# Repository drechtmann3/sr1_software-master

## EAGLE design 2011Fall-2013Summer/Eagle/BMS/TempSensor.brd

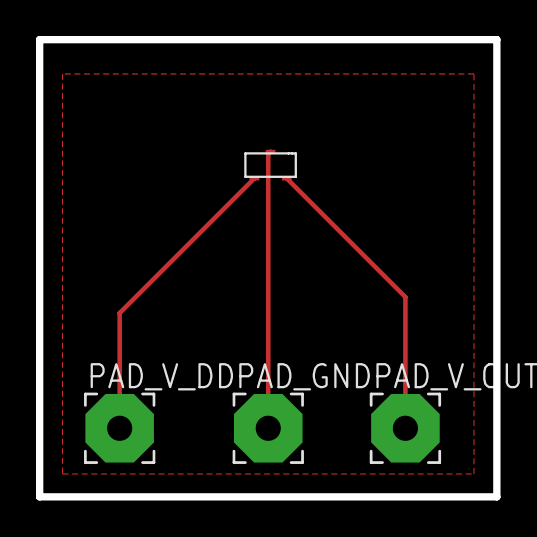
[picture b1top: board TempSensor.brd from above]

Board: 2 copper layers, 25.4 x 25.4 mm, 4 parts (0 on the bottom side), 3 nets.

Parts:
PAD_GND: 3,81/1,4
PAD_V_DD: 3,81/1,4
PAD_V_OUT: 3,81/1,4
U$1: MCP9701-SOT-23

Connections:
unnamed: PAD_V_DD.1, U$1.V_DD
unnamed: PAD_V_OUT.1, U$1.V_OUT
unnamed: PAD_GND.1, U$1.GND

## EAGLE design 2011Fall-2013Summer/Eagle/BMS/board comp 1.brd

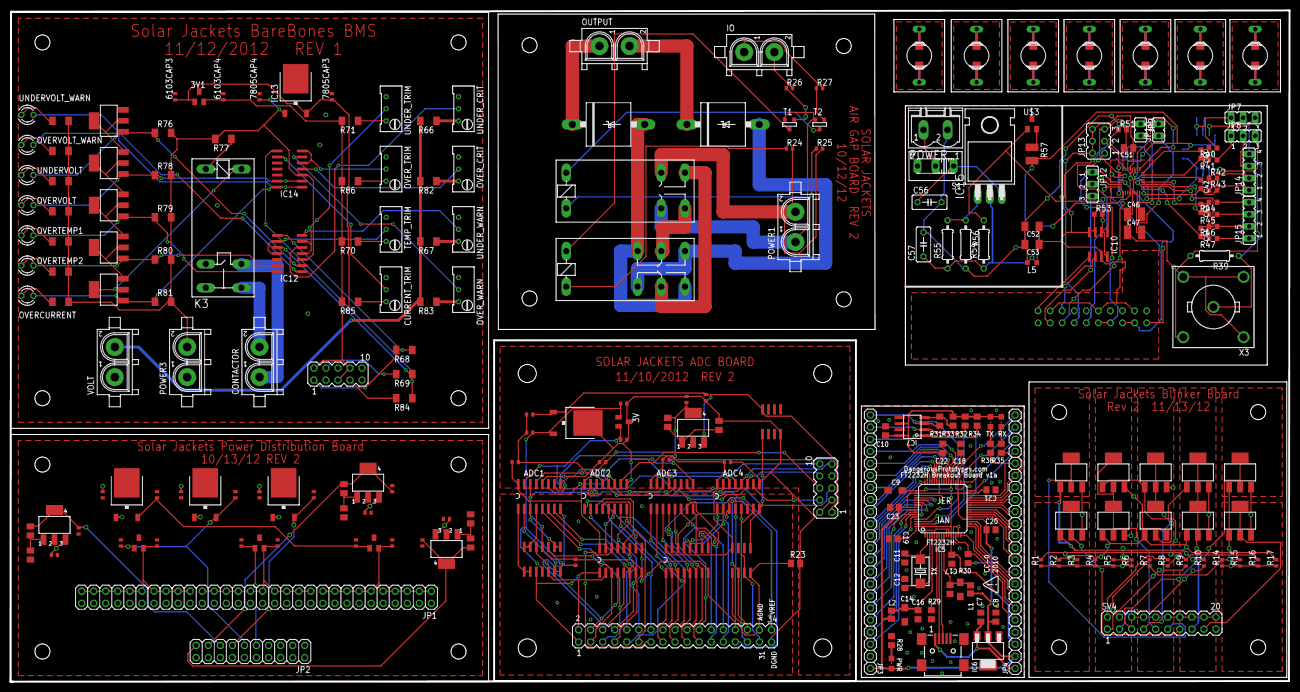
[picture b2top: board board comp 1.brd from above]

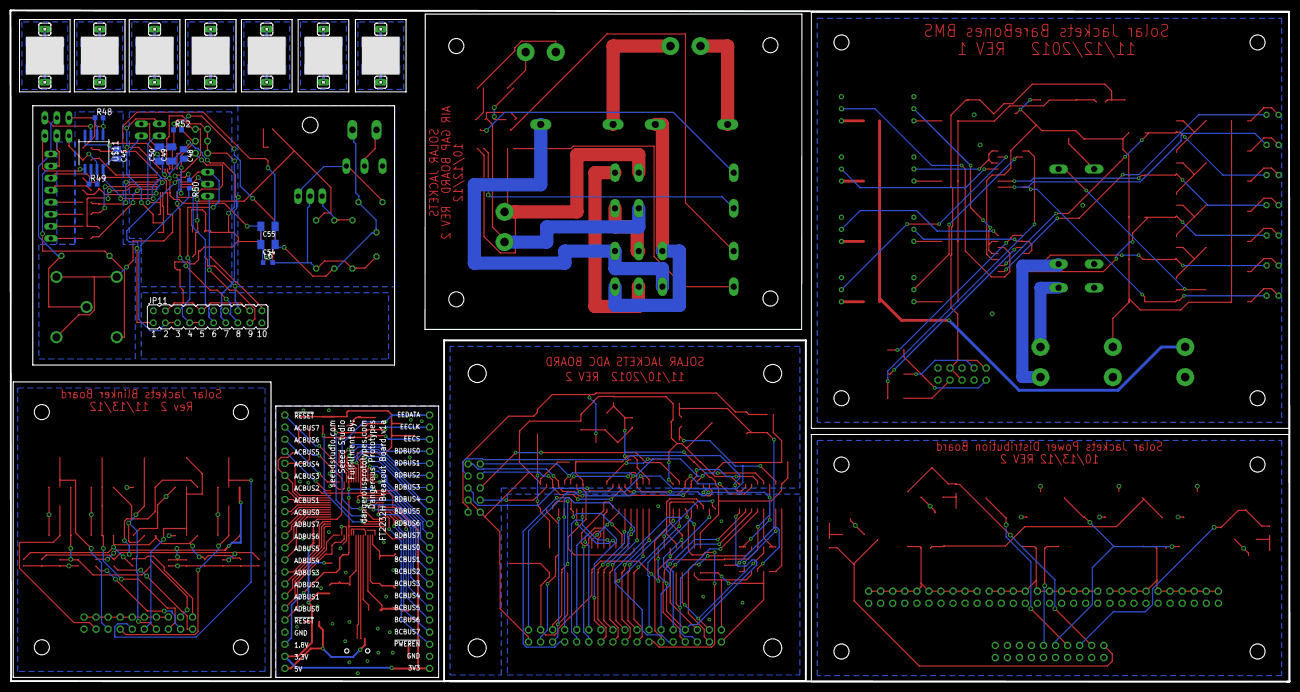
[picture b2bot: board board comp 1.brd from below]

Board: 2 copper layers, 269.4 x 141.4 mm, 280 parts (34 on the bottom side), 264 nets.

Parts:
3V, 3V1, 3V2, 3V3, 3V4: MAX6103; SOT23
5V: LM7805TV; TO252
317CAP1, 317CAP3, 317CAP5, 317CAP7, 7805CAP1: .33uF; C0402
317CAP2, 317CAP4, 317CAP6, 317CAP8, 6103CAP1, 6103CAP2, 6103CAP3, 6103CAP4, 6103CAP5, 6103CAP6, 6103CAP7, 6103CAP8, 6103CAP9, 6103CAP10, 7805CAP2, 7805CAP3, 7805CAP4: 1uF; C0402
6484CAP1: .1uF; C0402
ADC1, ADC2, ADC3, ADC4: MCP-3008; SO16
ADC_CAP1, ADC_CAP2, ADC_CAP3, ADC_CAP4: .1uF; C0402
BLINKER-L1, BLINKER-L2: N-HEXFET-2D_SOT232-; SOT223
BLINKER-R1, BLINKER-R2: N-HEXFET-2D_SOT232-; SOT223
BRAKE-C1, BRAKE-C2: N-HEXFET-2D_SOT232-; SOT223
BRAKE-L1, BRAKE-L2: N-HEXFET-2D_SOT232-; SOT223
BRAKE-R1, BRAKE-R2: N-HEXFET-2D_SOT232-; SOT223
C1, C2, C3, C4, C5, C6: 1uF; C0402
C7, C8, C10, C15, C16, C17, C18, C19, C20, C21, C22, C23: 0.1uF; C805
C9: 3.3uF; SMC_A
C11, C12: 27pF; C805
C13, C14: 4.7uF; SMC_A
C41, C42, C43, C44: 3900pF; C0603K
C45, C48, C51: 1uF; C0805K
C46, C47: 10uF; C1210K
C49, C50, C52, C53, C54, C55: 0.1uF; C1206K
C56, C57: C050-030X075
CONN1: CONN_USB; CONN_USB_MINI-B
CONTACTOR: 350428-1
CURRENT_TRIM: 1k; RTRIM64W
D1, D2: 5KPXX; P6T15
IC1, IC2, IC3, IC4: LM317; SOT223
IC5: FT2232H; LQFP64
IC6: SOT223
IC7: 93C46; SOIC8
IC10: 24LC256T; SO-08
IC12, IC14: LM339D; SO14
IC13: 7805DT; TO252
IC15: 317T; TO220H
IO: 350428-1
JP1: 2X30
JP2: 2X10
JP3, JP4: 1X22
JP7, JP8, JP12: JP2
JP9, JP10: JP1
JP11: JP10Q
JP13: JP3Q
JP14, JP15: JP4
K1: G2R2
K2: G2R2A
K3: G2REA
L1, L2: FB805
L5, L6: L2012C
LMC6484_1: LMC6484; SO14
NEWBATT, NEWBATT1, NEWBATT2, NEWBATT3, NEWBATT4, NEWBATT5, NEWBATT6: LQH55PN220MR0L
OLDBATT, OLDBATT1, OLDBATT2, OLDBATT3, OLDBATT4, OLDBATT5, OLDBATT6: NRS8040T0R9NJGJ
OUTPUT: 350428-1
OVERCURRENT: TLLG4400; LED3MM
OVERCURRENT_FET: N-HEXFET-2D_SOT232-; SOT223
OVERTEMP1, OVERTEMP2: TLLG4400; LED3MM
OVERTEMP1_FET, OVERTEMP2_FET: N-HEXFET-2D_SOT232-; SOT223
OVERVOLT: TLLG4400; LED3MM
OVERVOLT_FET: N-HEXFET-2D_SOT232-; SOT223
OVERVOLT_WARN: TLLG4400; LED3MM
OVER_CRIT: 10k; RTRIM64W
OVER_TRIM: 1k; RTRIM64W
OVER_WARN: 10K; RTRIM64W
POWER: MSTBV2
POWER1, POWER3: 350428-1
PWR: LED-805
PWR_1, PWR_2, PWR_3: 7805DT; TO252
R1, R2, R3, R4, R5, R6, R14, R15, R16, R17, R24, R25, R26, R27: 1k; R0402
R7, R8, R9, R10: 1K; R0402
R11, R13, R19, R21: 220; M0805
R12, R18, R20, R22: 361; M0805
R23: 0; M0805
R28, R35, R36: 470; R805
R29: 12k 1%; R805
R30, R32, R33, R34: 10k; R805
R31: 2.2k; R805
R39: 1M; 0207/10
R40, R41, R42, R43, R44, R45, R46, R47, R48, R49: 49.9; R0603
R50, R53: 33; R0603
R51, R52: 10K; R0603
R54: 150; 0207/10
R55: 240; 0207/10
R56: 725; 0207/10
R57: 0; R3225
R66, R67, R82, R83: 100k; M1406
R68, R69, R70, R71, R77, R85, R86: 100; M1406
R72, R73, R74, R75, R76, R78, R79, R80, R81, R84, R87, R88, R89: 1k; M1406
RX: LED-805
S1: 255SB
SV1: MA17-2
SV2, SV3: MA05-2
SV4: MA10-2
T1, T2: SOT-23
TEMP_TRIM: 1k; RTRIM64W
TX: LED-805
U$1: LM35; SO-08
U$2: ADS8386; ADS8363
U$3: LM4040; SOT23
U$4: DP_LOGO
U$5, U$9, U$10, U$12, U$13, U$14, U$15, U$16, U$17, U$18, U$19, U$20, U$21, U$22: SINGLE_HEADER
U$6, U$7: SP720APP; SO16
U$8: SP721APP; SO-08
U$11: OPA2365; SOP-08
UNDERVOLT: TLLG4400; LED3MM
UNDERVOLT_FET: N-HEXFET-2D_SOT232-; SOT223
UNDERVOLT_WARN: TLLG4400; LED3MM
UNDER_CRIT: 10k; RTRIM64W
UNDER_TRIM: 1k; RTRIM64W
UNDER_WARN: 10K; RTRIM64W
VOLT: 350428-1
X1: 12MHz; 4X6
X3: B35N57

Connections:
1.8V: C9.+, C17.1, C18.1, C19.1, IC5.12, IC5.37, IC5.49, IC5.64, JP4.3
3.3V: 317CAP2.1, ADC1.16, ADC2.16, ADC3.16, ADC4.16, ADC_CAP1.1, ADC_CAP2.1, ADC_CAP3.1, ADC_CAP4.1, IC4.4, R21.1, U$6.16, U$7.16, U$8.8
3.3V1: 317CAP8.1, IC3.4, JP2.19, R19.1
3.3V2: 317CAP4.1, IC2.4, JP2.15, R11.1
3.3V3: C8.1, C10.1, C20.1, C21.1, C22.1, C23.1, IC5.20, IC5.31, IC5.42, IC5.50, IC5.56, IC6.2, IC7.6, IC7.8, JP3.1, JP4.2, L1.2, L2.2, PWR.A, R30.1, R32.2, R33.2, R34.2, RX.A, TX.A
3.3V4: 317CAP6.1, IC1.4, JP2.17, R13.1
3.3V+: IC10.2, IC10.8, R53.2, R54.2, U$3.1
5V: 3V2.1, 6103CAP5.1, C2.1, PWR_1.2
5V1: C6.1, JP2.13, PWR_3.2
5V2: 3V.1, 5V.2, 6103CAP1.1, 6484CAP1.1, 7805CAP2.1, LMC6484_1.4
5V3: 3V1.1, 6103CAP3.1, 7805CAP3.1, IC13.2, SV3.2, SV3.5, SV3.8
5V4: 3V3.1, 6103CAP7.1, JP2.9
5V5: 3V4.1, 6103CAP9.1, C4.1, JP2.11, PWR_2.2
5V6: C7.1, CONN1.VUSB, IC6.3, JP4.1
5V+: C45.2, C48.2, C49.2, C50.2, C54.2, C55.2, L6.1, U$2.P$13_, U$2.P$29_, U$11.8
12V: 5V.1, 317CAP1.1, 7805CAP1.1, IC4.3, SV2.1, U$1.8
12V1: K2.P1, POWER1.2, R24.2, R25.2
12V2: 7805CAP4.1, IC12.3, IC13.1, IC14.3, POWER3.2, R72.2, R73.2, R74.2, R75.2, R76.2, R77.2, R78.2, R79.2, R80.2, R81.2, R87.2, R88.2, R89.2
12V3: SV4.6, SV4.8, SV4.10, SV4.12, SV4.14, SV4.16, SV4.18, SV4.20
12V4: 317CAP3.1, 317CAP5.1, 317CAP7.1, C1.1, C3.1, C5.1, IC1.3, IC2.3, IC3.3, JP2.1, JP2.3, JP2.5, JP2.7, PWR_1.1, PWR_2.1, PWR_3.1
96V: R66.2, R67.2, R82.2, R83.2, VOLT.2
!PWEREN: IC5.60, JP3.3
!RESET: IC5.14, JP4.5, R30.2
!SUSPEND: IC5.36, JP4.22
A1: ADC1.1, LMC6484_1.1, LMC6484_1.2
A2: ADC1.2, LMC6484_1.6, LMC6484_1.7
A3: ADC1.3, LMC6484_1.8, LMC6484_1.9
A4: ADC1.4, LMC6484_1.13, LMC6484_1.14
AC0: IC5.26, JP4.14
AC1: IC5.27, JP4.15
AC2: IC5.28, JP4.16
AC3: IC5.29, JP4.17, R35.1
AC4: IC5.30, JP4.18, R36.1
AC5: IC5.32, JP4.19
AC6: IC5.33, JP4.20
AC7: IC5.34, JP4.21
AD0: IC5.16, JP4.6
AD1: IC5.17, JP4.7
AD2: IC5.18, JP4.8
AD3: IC5.19, JP4.9
AD4: IC5.21, JP4.10
AD5: IC5.22, JP4.11
AD6: IC5.23, JP4.12
AD7: IC5.24, JP4.13
AGND: 6484CAP1.2, ADC1.14, ADC2.14, ADC3.14, ADC4.14, LMC6484_1.11, R23.1, SV1.32, U$6.8, U$7.8, U$8.4
BC0: IC5.48, JP3.11
BC1: IC5.52, JP3.10
BC2: IC5.53, JP3.9
BC3: IC5.54, JP3.8
BC4: IC5.55, JP3.7
BC5: IC5.57, JP3.6
BC6: IC5.58, JP3.5
BC7: IC5.59, JP3.4
BD0: IC5.38, JP3.19
BD1: IC5.39, JP3.18
BD2: IC5.40, JP3.17
BD3: IC5.41, JP3.16
BD4: IC5.43, JP3.15
BD5: IC5.44, JP3.14
BD6: IC5.45, JP3.13
BD7: IC5.46, JP3.12
BLINKER_L: BLINKER-L1.1, BLINKER-L2.1, R5.2, R6.2, R10.2
BLINKER_L_BACK_-: BLINKER-L2.2, BLINKER-L2.4, SV4.13
BLINKER_L_FRONT_-: BLINKER-L1.2, BLINKER-L1.4, SV4.11
BLINKER_R: BLINKER-R1.1, BLINKER-R2.1, R7.1, R14.2, R15.2
BLINKER_R_BACK_-: BLINKER-R2.2, BLINKER-R2.4, SV4.17
BLINKER_R_FRONT_-: BLINKER-R1.2, BLINKER-R1.4, SV4.15
BRAKE: BRAKE-C1.1, BRAKE-L1.1, BRAKE-R1.1, R1.2, R3.2, R9.2, R16.2
BRAKE_C_-: BRAKE-C1.2, BRAKE-C1.4, BRAKE-C2.2, BRAKE-C2.4, SV4.7
BRAKE_L_-: BRAKE-L1.2, BRAKE-L1.4, BRAKE-L2.2, BRAKE-L2.4, SV4.9
BRAKE_REGEN: BRAKE-C2.1, BRAKE-L2.1, BRAKE-R2.1, R2.2, R4.2, R8.1, R17.2
BRAKE_R_-: BRAKE-R1.2, BRAKE-R1.4, BRAKE-R2.2, BRAKE-R2.4, SV4.5
CONTACTOR_IN: CONTACTOR.2, K3.S@
CONTACTOR_OUT: CONTACTOR.1, K3.P@
CURRENT: R84.2, SV3.7
D5V+: C51.2, C52.2, C53.2, L5.2, R51.2, R52.2, U$2.P$27_
DC+: POWER.1, S1.2
DGND0: C51.1, C52.1, C53.1, IC10.1, IC10.3, IC10.4, IC10.7, JP11.4, JP11.10, JP11.18, JP13.2, JP13.4, JP13.6, R53.1, U$2.P$28_
DIR: IO.2, R26.2
DM: CONN1.D-, IC5.7
DP: CONN1.D+, IC5.8
EECLK: IC5.62, IC7.2, JP3.21, R32.1
EECS: IC5.63, IC7.1, JP3.20, R34.1
EEDATA: IC5.61, IC7.3, JP3.22, R31.2
GND: BLINKER-L1.3, BLINKER-L2.3, BLINKER-R1.3, BLINKER-R2.3, BRAKE-C1.3, BRAKE-C2.3, BRAKE-L1.3, BRAKE-L2.3, BRAKE-R1.3, BRAKE-R2.3, R1.1, R2.1, R3.1, R4.1, R5.1, R6.1, R14.1, R15.1, R16.1, R17.1, SV4.19
GND0: C45.1, C46.1, C47.1, C48.1, C49.1, C50.1, C54.1, C55.1, C56.2, C57.2, POWER.2, R56.2, R57.2, U$2.P$11_, U$2.P$12_, U$2.P$30_, U$11.4, X3.3, X3.4, X3.5
GND1: 3V2.3, 3V3.3, 3V4.3, 317CAP3.2, 317CAP4.2, 317CAP5.2, 317CAP6.2, 317CAP7.2, 317CAP8.2, 6103CAP5.2, 6103CAP6.2, 6103CAP7.2, 6103CAP8.2, 6103CAP9.2, 6103CAP10.2, C1.2, C2.2, C3.2, C4.2, C5.2, C6.2, JP1.2, JP1.4, JP1.6, JP1.8, JP1.10, JP1.12, JP1.14, JP1.16, JP1.18, JP1.20, JP1.22, JP1.24, JP1.26, JP1.28, JP1.30, JP1.32, JP1.34, JP1.36, JP1.38, JP1.40, JP1.42, JP1.44, JP1.46, JP1.48, JP1.50, JP1.52, JP1.54, JP1.56, JP1.58, JP1.60, JP2.2, JP2.4, JP2.6, JP2.8, JP2.10, JP2.12, JP2.14, JP2.16, JP2.18, JP2.20, PWR_1.3, PWR_2.3, PWR_3.3, R12.2, R18.2, R20.2
GND4: R57.1, U$3.2
GND5: 3V.3, 5V.3, 317CAP1.2, 317CAP2.2, 6103CAP1.2, 6103CAP2.2, 7805CAP1.2, 7805CAP2.2, ADC1.9, ADC2.9, ADC3.9, ADC4.9, ADC_CAP1.2, ADC_CAP2.2, ADC_CAP3.2, ADC_CAP4.2, R22.2, R23.2, SV1.33, SV2.2, SV2.3, U$1.4
GND6: K2.P2, POWER1.1, T1.2, T2.2
GND7: C7.2, C8.2, C9.-, C10.2, C11.2, C12.2, C13.-, C14.-, C15.2, C16.2, C17.2, C18.2, C19.2, C20.2, C21.2, C22.2, C23.2, CONN1.GND, IC5.1, IC5.5, IC5.10, IC5.11, IC5.13, IC5.15, IC5.25, IC5.35, IC5.47, IC5.51, IC6.1, IC7.5, JP3.2, JP4.4, R28.1, R29.1
GND8: 3V1.3, 6103CAP3.2, 6103CAP4.2, 7805CAP3.2, 7805CAP4.2, CURRENT_TRIM.1, IC12.12, IC13.3, IC14.12, OVER_CRIT.1, OVER_TRIM.1, OVER_WARN.1, POWER3.1, SV3.3, SV3.6, SV3.9, TEMP_TRIM.1, UNDERVOLT_FET.3, UNDER_CRIT.1, UNDER_TRIM.1, UNDER_WARN.1, VOLT.1
IN1: LMC6484_1.3, SV1.1, U$6.1
IN2: LMC6484_1.5, SV1.2, U$6.2
IN3: LMC6484_1.10, SV1.3, U$6.3
IN4: LMC6484_1.12, SV1.4, U$6.4
IN5: ADC1.5, SV1.5, U$6.5
IN6: ADC1.6, SV1.6, U$6.6
IN7: ADC1.7, SV1.7, U$6.7
IN8: ADC1.8, SV1.8, U$6.9
IN9: ADC2.1, SV1.9, U$6.10
IN10: ADC2.2, SV1.10, U$6.11
IN11: ADC2.3, SV1.11, U$6.12
IN12: ADC2.4, SV1.12, U$6.13
IN13: ADC2.5, SV1.13, U$6.14
IN14: ADC2.6, SV1.14, U$6.15
IN15: ADC2.7, SV1.15, U$7.1
IN16: ADC2.8, SV1.16, U$7.2
IN17: ADC3.1, SV1.17, U$7.3
IN18: ADC3.2, SV1.18, U$7.4
IN19: ADC3.3, SV1.19, U$7.5
IN20: ADC3.4, SV1.20, U$7.6
IN21: ADC3.5, SV1.21, U$7.7
IN22: ADC3.6, SV1.22, U$7.9
IN23: ADC3.7, SV1.23, U$7.10
IN24: ADC3.8, SV1.24, U$7.11
IN25: ADC4.1, SV1.25, U$7.12
IN26: ADC4.2, SV1.26, U$7.13
IN27: ADC4.3, SV1.27, U$7.14
IN28: ADC4.4, SV1.28, U$7.15
IN29: ADC4.5, SV1.29, U$8.1
IN30: ADC4.6, SV1.30, U$8.2
IN31: ADC4.7, SV1.31, U$8.3
IN32: ADC4.8, U$1.1, U$8.5
MOTOR+: D2.C, OUTPUT.2
MOTOR+_PRE: D2.A, K1.O2, K1.S1
MOTOR-: D1.C, OUTPUT.1
MOTOR-_PRE: D1.A, K1.O1, K1.S2
unnamed: R8.2, SV4.2
unnamed: R7.2, SV4.4
unnamed: R9.1, SV4.1
unnamed: R10.1, SV4.3
unnamed: IC2.1, R11.2, R12.1
unnamed: IC1.1, R13.2, R18.1
unnamed: IC3.1, R19.2, R20.1
unnamed: IC4.1, R21.2, R22.1
unnamed: K1.P2, K2.S1
unnamed: K1.P1, K2.S2
unnamed: K1.1, R24.1
unnamed: K2.1, R25.1
unnamed: K1.2, T1.1
unnamed: K2.2, T2.1
unnamed: R27.1, T2.3
unnamed: R26.1, T1.3
unnamed: IC5.6, R29.2
unnamed: C11.1, IC5.2, X1.1
unnamed: C12.1, IC5.3, X1.2
unnamed: PWR.C, R28.2
unnamed: R35.2, RX.C
unnamed: R36.2, TX.C
unnamed: C41.1, R40.2, U$2.P$1_
unnamed: C41.2, R41.2, U$2.P$2_
unnamed: C42.1, R42.2, U$2.P$3_
unnamed: C42.2, R43.2, U$2.P$4_
unnamed: C43.1, R44.2, U$2.P$5_
unnamed: C43.2, R45.2, U$2.P$6_
unnamed: C44.1, R46.2, U$2.P$7_
unnamed: C44.2, R47.2, U$2.P$8_
unnamed: JP7.1, R40.1, R48.2, U$11.1
unnamed: R48.1, U$11.2
unnamed: JP7.3, U$11.3
unnamed: JP8.1, R41.1, R49.2, U$11.7
unnamed: R49.1, U$11.6
unnamed: JP8.3, U$11.5
unnamed: JP14.2, R42.1
unnamed: JP14.1, R43.1
unnamed: JP15.4, R44.1
unnamed: JP15.3, R45.1
unnamed: JP15.2, R46.1
unnamed: JP15.1, R47.1
unnamed: C46.2, JP9.2, U$2.P$9_
unnamed: JP9.1, U$2.P$32_
unnamed: IC7.4, R31.1, R33.1
unnamed: JP10.2, U$2.P$31_
unnamed: C47.2, JP10.1, U$2.P$10_
unnamed: C14.+, C16.1, IC5.4, L2.1
unnamed: C13.+, C15.1, IC5.9, L1.1
unnamed: JP11.1, U$2.P$21_
unnamed: R50.1, U$2.P$22_
unnamed: JP11.3, JP11.5, R50.2
unnamed: JP11.7, JP11.9, JP12.1, U$2.P$20_
unnamed: JP11.11, U$2.P$18_
unnamed: JP11.13, U$2.P$25_
unnamed: JP11.15, U$2.P$23_
unnamed: JP12.2, U$2.P$19_
unnamed: JP11.17, JP12.3
unnamed: JP13.1, U$2.P$16_
unnamed: JP13.3, R51.1, U$2.P$17_
unnamed: JP13.5, R52.1, U$2.P$24_
unnamed: IC10.5, JP11.20
unnamed: IC10.6, JP11.16
unnamed: C57.1, IC15.2, L5.1, L6.2, R54.1, R55.1
unnamed: IC15.1, R55.2, R56.1
unnamed: C56.1, IC15.3, S1.1
unnamed: NEWBATT.P$2, OLDBATT.P$2, U$5.P$1
unnamed: NEWBATT.P$1, OLDBATT.P$1, U$9.P$1
unnamed: NEWBATT1.P$2, OLDBATT1.P$2, U$10.P$1
unnamed: NEWBATT1.P$1, OLDBATT1.P$1, U$12.P$1
unnamed: NEWBATT2.P$2, OLDBATT2.P$2, U$13.P$1
unnamed: NEWBATT2.P$1, OLDBATT2.P$1, U$14.P$1
unnamed: NEWBATT3.P$2, OLDBATT3.P$2, U$15.P$1
unnamed: NEWBATT3.P$1, OLDBATT3.P$1, U$16.P$1
unnamed: NEWBATT4.P$2, OLDBATT4.P$2, U$17.P$1
unnamed: NEWBATT4.P$1, OLDBATT4.P$1, U$18.P$1
unnamed: NEWBATT5.P$2, OLDBATT5.P$2, U$19.P$1
unnamed: NEWBATT5.P$1, OLDBATT5.P$1, U$20.P$1
unnamed: NEWBATT6.P$2, OLDBATT6.P$2, U$21.P$1
unnamed: NEWBATT6.P$1, OLDBATT6.P$1, U$22.P$1
unnamed: IC12.7, UNDER_WARN.2
unnamed: IC12.5, UNDER_CRIT.2
unnamed: IC12.9, IC12.11, TEMP_TRIM.2
unnamed: R66.1, UNDER_CRIT.3
unnamed: R67.1, UNDER_WARN.3
unnamed: IC12.4, IC12.6, UNDER_TRIM.2
unnamed: R71.1, UNDER_TRIM.3
unnamed: R70.1, TEMP_TRIM.3
unnamed: R72.1, UNDERVOLT.A
unnamed: R73.1, UNDERVOLT_WARN.A
unnamed: OVERTEMP1.A, R74.1
unnamed: OVERTEMP2.A, R75.1
unnamed: K3.1, R77.1
unnamed: CURRENT_TRIM.2, IC14.9
unnamed: OVER_WARN.3, R83.1
unnamed: IC14.5, IC14.7, OVER_TRIM.2
unnamed: OVER_TRIM.3, R86.1
unnamed: CURRENT_TRIM.3, R85.1
unnamed: OVERVOLT.A, R87.1
unnamed: OVERVOLT_WARN.A, R88.1
unnamed: OVERCURRENT.A, R89.1
unnamed: K3.2, OVERCURRENT_FET.2, OVERCURRENT_FET.4
unnamed: OVERCURRENT_FET.3, OVERTEMP2_FET.2, OVERTEMP2_FET.4
unnamed: OVERTEMP1_FET.2, OVERTEMP1_FET.4, OVERTEMP2_FET.3
unnamed: OVERTEMP1_FET.3, OVERVOLT_FET.2, OVERVOLT_FET.4
unnamed: OVERVOLT_FET.3, UNDERVOLT_FET.2, UNDERVOLT_FET.4
unnamed: IC14.6, OVER_WARN.2
unnamed: IC14.4, OVER_CRIT.2
unnamed: OVER_CRIT.3, R82.1
unnamed: IC14.8, R84.1
unnamed: IC12.8, R68.1
unnamed: IC12.10, R69.1
ON: IO.1, R27.2
OVERCURRENT_CRITICAL: IC14.14, OVERCURRENT.K, OVERCURRENT_FET.1, R81.1
OVERTEMP_CRITICAL1: IC12.14, OVERTEMP1.K, OVERTEMP1_FET.1, R79.1
OVERTEMP_CRITICAL2: IC12.13, OVERTEMP2.K, OVERTEMP2_FET.1, R80.1
OVERVOLT_CRITICAL: IC14.2, OVERVOLT.K, OVERVOLT_FET.1, R78.1
OVERVOLT_WARNING1: IC14.1, OVERVOLT_WARN.K
SIGNALGND: JP8.2, JP14.3, R39.2, X3.2
SIGNALV+: JP7.2, JP14.4, R39.1, X3.1
SPI_CLK: ADC1.13, ADC2.13, ADC3.13, ADC4.13, SV2.10
SPI_CS1: ADC1.10, SV2.7
SPI_CS2: ADC2.10, SV2.6
SPI_CS3: ADC3.10, SV2.5
SPI_CS4: ADC4.10, SV2.4
SPI_DIN: ADC1.11, ADC2.11, ADC3.11, ADC4.11, SV2.8
SPI_DOUT: ADC1.12, ADC2.12, ADC3.12, ADC4.12, SV2.9
TEMP1: R68.2, SV3.1
TEMP2: R69.2, SV3.4
UNDERVOLT_CRITICAL: IC12.2, R76.1, UNDERVOLT.K, UNDERVOLT_FET.1
UNDERVOLT_WARNING: IC12.1, UNDERVOLT_WARN.K
VREF: 3V.2, 6103CAP2.1, ADC1.15, ADC2.15, ADC3.15, ADC4.15, SV1.34
VREF1: 3V1.2, 6103CAP4.1, R70.2, R71.2, R85.2, R86.2
VREF2: 3V2.2, 6103CAP6.1, JP1.1, JP1.3, JP1.5, JP1.7, JP1.9, JP1.11, JP1.13, JP1.15, JP1.17, JP1.19
VREF3: 3V3.2, 6103CAP8.1, JP1.21, JP1.23, JP1.25, JP1.27, JP1.29, JP1.31, JP1.33, JP1.35, JP1.37, JP1.39
VREF4: 3V4.2, 6103CAP10.1, JP1.41, JP1.43, JP1.45, JP1.47, JP1.49, JP1.51, JP1.53, JP1.55, JP1.57, JP1.59

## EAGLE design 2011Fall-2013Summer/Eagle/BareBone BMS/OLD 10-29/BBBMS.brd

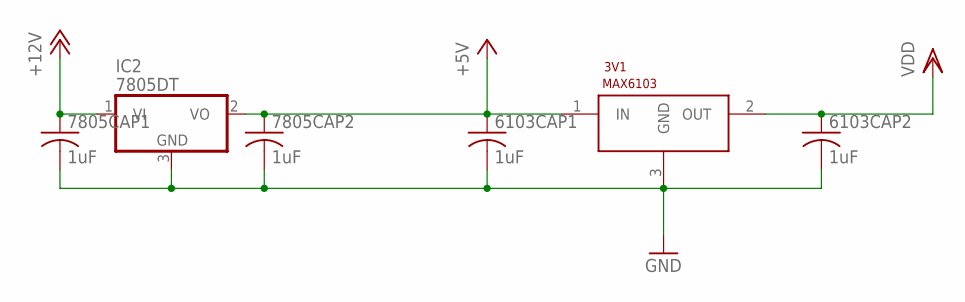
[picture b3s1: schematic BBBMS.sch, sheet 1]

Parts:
3V1: MAX6103; SOT23
6103CAP1, 6103CAP2, 7805CAP1, 7805CAP2: 1uF; C1206
IC2: 7805DT; TO252

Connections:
5V: 3V1.1 (IN), 6103CAP1.1, 7805CAP2.1, IC2.2 (VO); also elsewhere on the board
12V: 7805CAP1.1, IC2.1 (VI); also elsewhere on the board
GND: 3V1.3 (GND), 6103CAP1.2, 6103CAP2.2, 7805CAP1.2, 7805CAP2.2, IC2.3 (GND); also elsewhere on the board
VREF: 3V1.2 (OUT), 6103CAP2.1; also elsewhere on the board

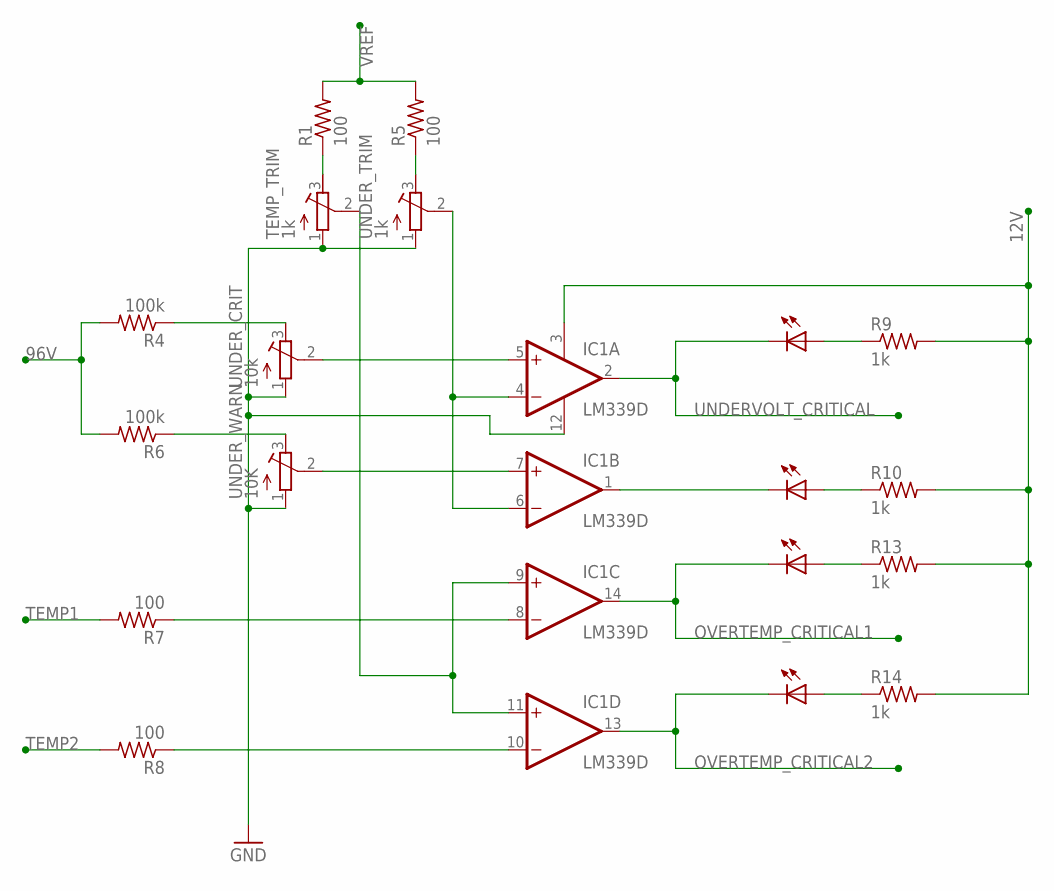
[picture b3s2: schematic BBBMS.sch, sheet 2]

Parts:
IC1: LM339D; SO14
OVERTEMP1, OVERTEMP2: TLLG4400; LED3MM
R1, R5, R7, R8: 100; R1206
R4, R6: 100k; R1206
R9, R10, R13, R14: 1k; R1206
TEMP_TRIM: 1k; RTRIM64W
UNDERVOLT: TLLG4400; LED3MM
UNDERVOLT_WARN: TLLG4400; LED3MM
UNDER_CRIT: 10k; RTRIM64W
UNDER_TRIM: 1k; RTRIM64W
UNDER_WARN: 10K; RTRIM64W

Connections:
12V: IC1.3 (V+), R9.2, R10.2, R13.2, R14.2; also elsewhere on the board
96V: R4.2, R6.2; also elsewhere on the board
GND: IC1.12 (GND), TEMP_TRIM.1 (A), UNDER_CRIT.1 (A), UNDER_TRIM.1 (A), UNDER_WARN.1 (A); also elsewhere on the board
unnamed: IC1.8 (-IN), R7.1
unnamed: IC1.7 (+IN), UNDER_WARN.2 (S)
unnamed: IC1.5 (+IN), UNDER_CRIT.2 (S)
unnamed: IC1.9 (+IN), IC1.11 (+IN), TEMP_TRIM.2 (S)
unnamed: R6.1, UNDER_WARN.3 (E)
unnamed: IC1.10 (-IN), R8.1
unnamed: R4.1, UNDER_CRIT.3 (E)
unnamed: IC1.4 (-IN), IC1.6 (-IN), UNDER_TRIM.2 (S)
unnamed: R5.1, UNDER_TRIM.3 (E)
unnamed: R1.1, TEMP_TRIM.3 (E)
unnamed: R9.1, UNDERVOLT.A
unnamed: R10.1, UNDERVOLT_WARN.A
unnamed: OVERTEMP1.A, R13.1
unnamed: OVERTEMP2.A, R14.1
OVERTEMP_CRITICAL1: IC1.14 (OUT), OVERTEMP1.K (C); also elsewhere on the board
OVERTEMP_CRITICAL2: IC1.13 (OUT), OVERTEMP2.K (C); also elsewhere on the board
TEMP1: R7.2; also elsewhere on the board
TEMP2: R8.2; also elsewhere on the board
UNDERVOLT_CRITICAL: IC1.2 (OUT), UNDERVOLT.K (C); also elsewhere on the board
UNDERVOLT_WARNING: IC1.1 (OUT), UNDERVOLT_WARN.K (C)
VREF: R1.2, R5.2; also elsewhere on the board

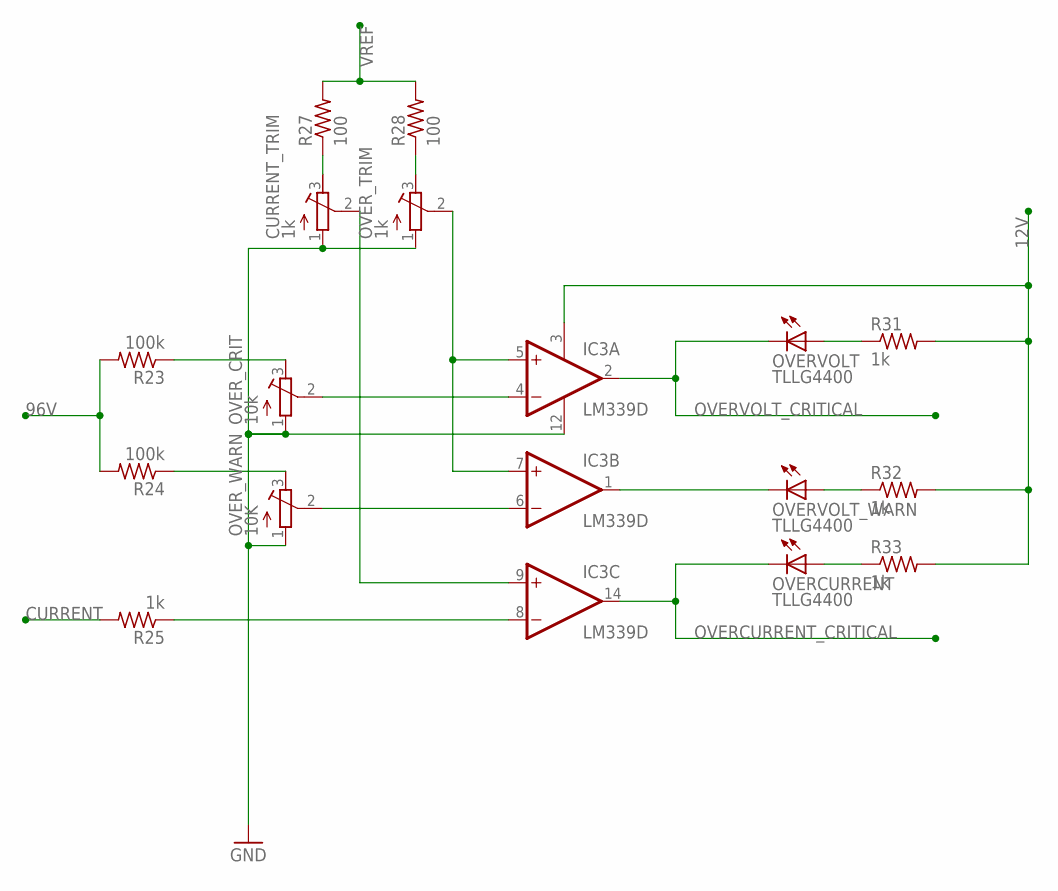
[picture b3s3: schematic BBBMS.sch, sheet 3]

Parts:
CURRENT_TRIM: 1k; RTRIM64W
IC3: LM339D; SO14
OVERCURRENT: TLLG4400; LED3MM
OVERVOLT: TLLG4400; LED3MM
OVERVOLT_WARN: TLLG4400; LED3MM
OVER_CRIT: 10k; RTRIM64W
OVER_TRIM: 1k; RTRIM64W
OVER_WARN: 10K; RTRIM64W
R23, R24: 100k; R1206
R25, R31, R32, R33: 1k; R1206
R27, R28: 100; R1206

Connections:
12V: IC3.3 (V+), R31.2, R32.2, R33.2; also elsewhere on the board
96V: R23.2, R24.2; also elsewhere on the board
CURRENT: R25.2; also elsewhere on the board
GND: CURRENT_TRIM.1 (A), IC3.12 (GND), OVER_CRIT.1 (A), OVER_TRIM.1 (A), OVER_WARN.1 (A); also elsewhere on the board
unnamed: IC3.6 (-IN), OVER_WARN.2 (S)
unnamed: IC3.4 (-IN), OVER_CRIT.2 (S)
unnamed: CURRENT_TRIM.2 (S), IC3.9 (+IN)
unnamed: OVER_CRIT.3 (E), R23.1
unnamed: OVER_WARN.3 (E), R24.1
unnamed: IC3.8 (-IN), R25.1
unnamed: IC3.5 (+IN), IC3.7 (+IN), OVER_TRIM.2 (S)
unnamed: OVER_TRIM.3 (E), R28.1
unnamed: CURRENT_TRIM.3 (E), R27.1
unnamed: OVERVOLT.A, R31.1
unnamed: OVERVOLT_WARN.A, R32.1
unnamed: OVERCURRENT.A, R33.1
OVERCURRENT_CRITICAL: IC3.14 (OUT), OVERCURRENT.K (C); also elsewhere on the board
OVERVOLT_CRITICAL: IC3.2 (OUT), OVERVOLT.K (C); also elsewhere on the board
OVERVOLT_WARNING1: IC3.1 (OUT), OVERVOLT_WARN.K (C)
VREF: R27.2, R28.2; also elsewhere on the board

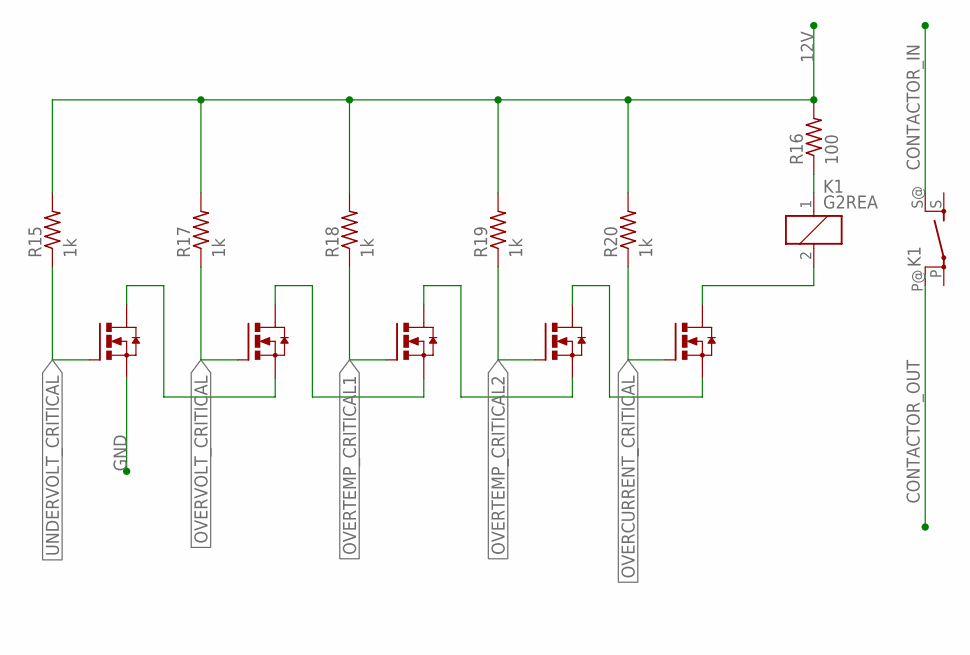
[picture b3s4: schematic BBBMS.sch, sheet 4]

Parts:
K1: G2REA
OVERCURRENT_FET: N-HEXFET-2D_SOT232-; SOT223
OVERTEMP1_FET, OVERTEMP2_FET: N-HEXFET-2D_SOT232-; SOT223
OVERVOLT_FET: N-HEXFET-2D_SOT232-; SOT223
R15, R17, R18, R19, R20: 1k; R1206
R16: 100; R1206
UNDERVOLT_FET: N-HEXFET-2D_SOT232-; SOT223

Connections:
12V: R15.2, R16.2, R17.2, R18.2, R19.2, R20.2; also elsewhere on the board
CONTACTOR_IN: K1.S@ (S); also elsewhere on the board
CONTACTOR_OUT: K1.P@; also elsewhere on the board
GND: UNDERVOLT_FET.3 (S); also elsewhere on the board
unnamed: K1.2, OVERCURRENT_FET.2 (D), OVERCURRENT_FET.4 (D)
unnamed: OVERCURRENT_FET.3 (S), OVERTEMP2_FET.2 (D), OVERTEMP2_FET.4 (D)
unnamed: K1.1, R16.1
unnamed: OVERTEMP1_FET.2 (D), OVERTEMP1_FET.4 (D), OVERTEMP2_FET.3 (S)
unnamed: OVERTEMP1_FET.3 (S), OVERVOLT_FET.2 (D), OVERVOLT_FET.4 (D)
unnamed: OVERVOLT_FET.3 (S), UNDERVOLT_FET.2 (D), UNDERVOLT_FET.4 (D)
OVERCURRENT_CRITICAL: OVERCURRENT_FET.1 (G), R20.1; also elsewhere on the board
OVERTEMP_CRITICAL1: OVERTEMP1_FET.1 (G), R18.1; also elsewhere on the board
OVERTEMP_CRITICAL2: OVERTEMP2_FET.1 (G), R19.1; also elsewhere on the board
OVERVOLT_CRITICAL: OVERVOLT_FET.1 (G), R17.1; also elsewhere on the board
UNDERVOLT_CRITICAL: R15.1, UNDERVOLT_FET.1 (G); also elsewhere on the board

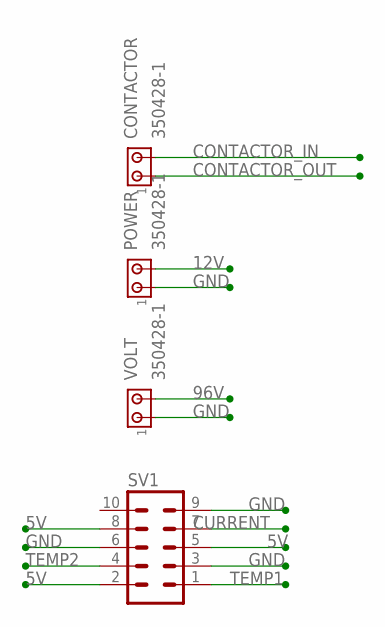
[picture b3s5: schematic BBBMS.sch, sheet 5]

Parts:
CONTACTOR: 350428-1
POWER: 350428-1
SV1: MA05-2
VOLT: 350428-1

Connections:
5V: SV1.2, SV1.5, SV1.8; also elsewhere on the board
12V: POWER.2; also elsewhere on the board
96V: VOLT.2; also elsewhere on the board
CONTACTOR_IN: CONTACTOR.2; also elsewhere on the board
CONTACTOR_OUT: CONTACTOR.1; also elsewhere on the board
CURRENT: SV1.7; also elsewhere on the board
GND: POWER.1, SV1.3, SV1.6, SV1.9, VOLT.1; also elsewhere on the board
TEMP1: SV1.1; also elsewhere on the board
TEMP2: SV1.4; also elsewhere on the board
